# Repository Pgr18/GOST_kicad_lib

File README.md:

# <strong> Схема электрическая принципиальная "Светодиодная цветомузыка" </strong>

Цель работы: реализация схемы электрической принципиальной "Светодиодная цветомузыка" с использованием среды KiCAD.

На рисунке 1 представлена электрическая принципиальная схема светодиодной цветомузыки.  

<image src="https://github.com/Pgr18/GOST_kicad_lib/blob/Prohorova-Christina/Plata%201111.png"  alt="Рисунок 1 - Принципиальная схема устройства">

Рисунок 1 - Принципиальная схема Светодиодной цветомузыки

Для корректной работы устройства необходим усилитель, который является частью схемы, изображенной выше. Принципиальная схема усилителя представлена на рисунке 2.  

<image src="https://github.com/Pgr18/GOST_kicad_lib/blob/Prohorova-Christina/%D0%A0%D0%B8%D1%81%D1%83%D0%BD%D0%BE%D0%BA%202%20%D0%A1%D0%AD%D0%9F%20%D1%83%D1%81%D0%B8%D0%BB%D0%B8%D1%82%D0%B5%D0%BB%D1%8C.jpg"  alt="Рисунок 2 - Принципиальная схема усилителя">

Рисунок 2 - Принципиальная схема усилителя сигнала

Элементная база вышеупомянутой схемы включает в себя:
- Резисторы: 200 Ом – 3 шт., 500 Ом – 2 шт., 1 кОм – 2 шт., 10 кОм – 1 шт,  47 кОм – 1 шт.;
- Подстрочные резисторы: 47 кОм – 3 шт., 100 кОм – 1 шт.;
- Транзисторы: 4 шт.;
- Светодиоды: зеленый - 1 шт., синий - 1 шт., красный - 1 шт.;
- Неполярные конденсаторы: 100 нФ – 1 шт., 150 нФ – 1 шт., 330 нФ – 1 шт., 680 нФ – 1 шт., 10 мкФ – 2 шт

Подбор элементов для реализации схемы осуществлялся с использованием сайта *[ChipDip](https://www.chipdip.ru/)*. После этого для каждого элемента были подобраны посадочные места и модели, взятые из общедоступных источников: *[Snap EDA](https://www.snapeda.com/)* и *[Electronic Component Search Engine](https://componentsearchengine.com/)*.

Следующим этапом был перенос принципиальной схемы на макет печатной платы. В соответствии со связями между элементами была проведена трассировка платы. Ширина дорожек составляла 0,5 мм.

После этого была проведена сплошная заливка макета платы медью. На поверхность платы были нанесены обозначения элементов схемы, а также обозначения внешних контактов платы.

На рисунке 3 представлен результат проделанной работы

<image src="https://github.com/Pgr18/GOST_kicad_lib/blob/Prohorova-Christina/plata11.png" alt="Рисунок 3 - Печатная плата">
Рисунок 3 - Печатная плата

На рисунке 4 представлена 3D-модель печатной платы.

<image src="https://github.com/Pgr18/GOST_kicad_lib/blob/Prohorova-Christina/3dplata.png" alt= "Рисунок 4 - 3D модель печатной платы">
  
Рисунок 4 - 3D модель печатной платы

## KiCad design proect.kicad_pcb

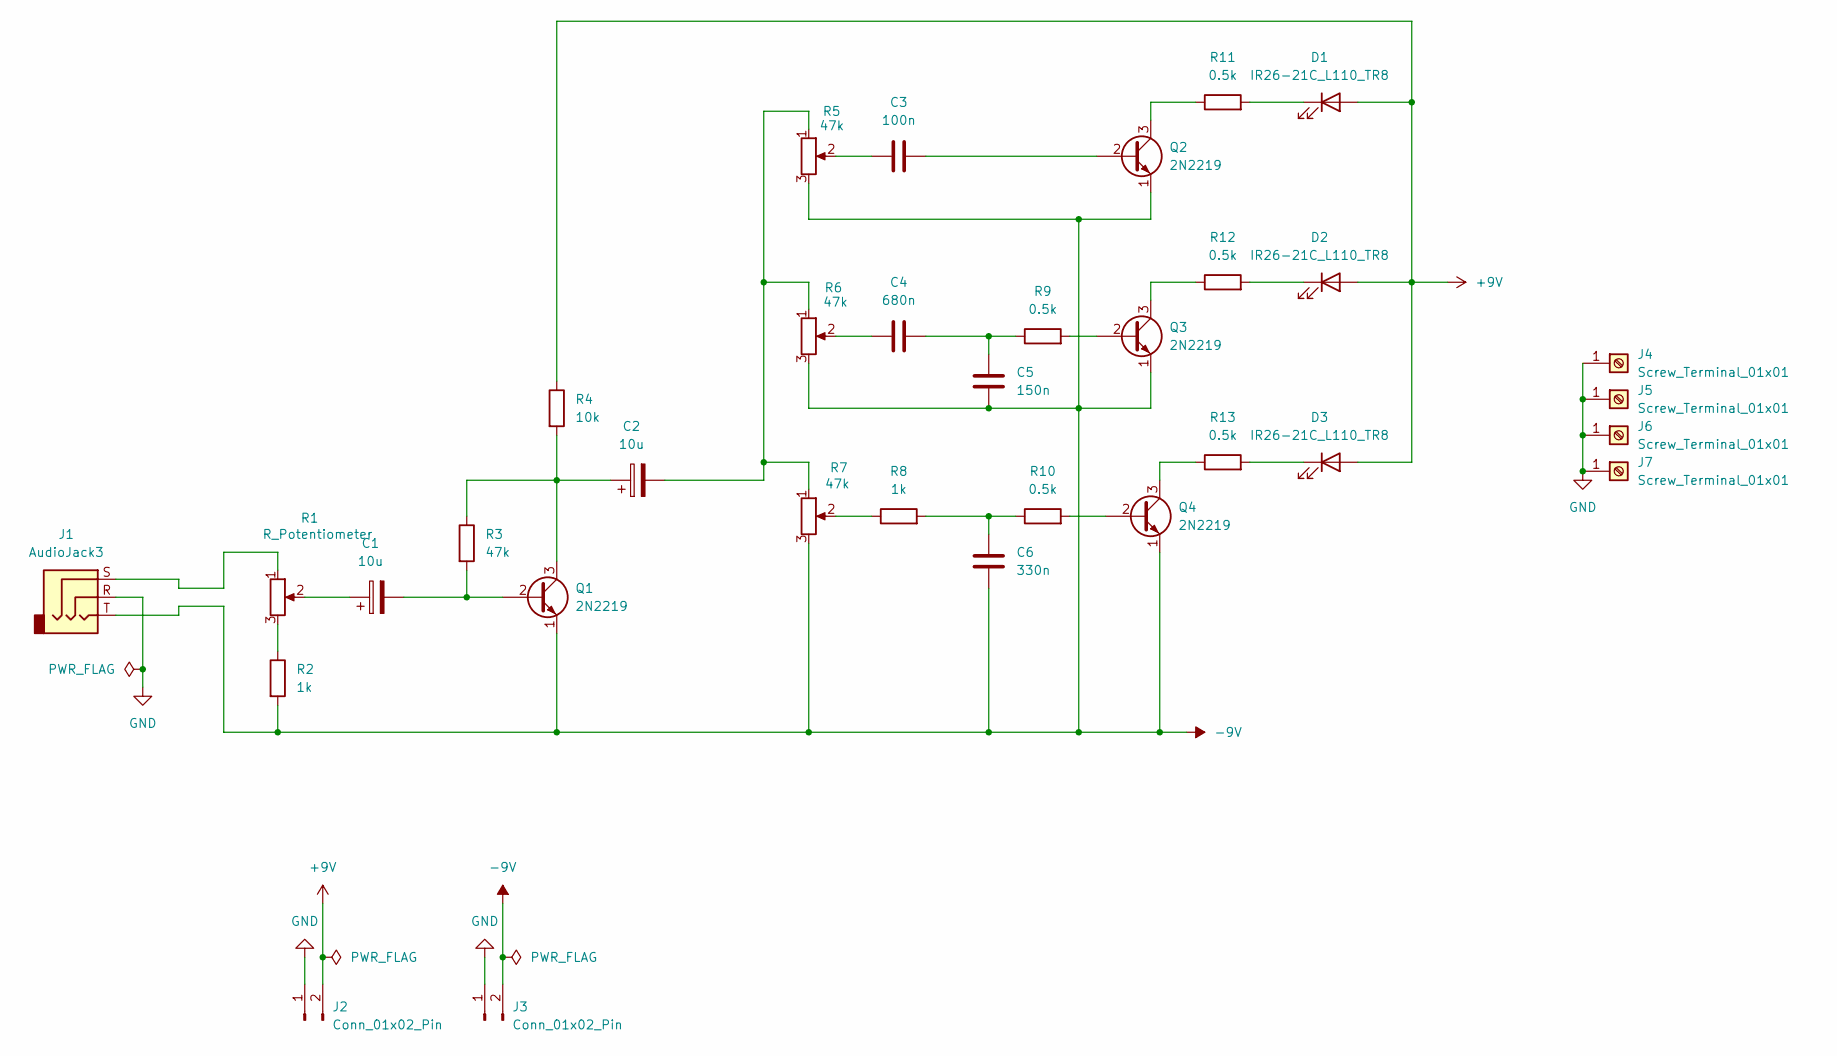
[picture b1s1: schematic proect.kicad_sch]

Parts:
C1, C2: 10u; C_1206_3216Metric
C3: 100n; C_0201_0603Metric
C4: 680n; C_0201_0603Metric
C5: 150n; C_0201_0603Metric
C6: 330n; C_0201_0603Metric
D1, D2, D3: IR26-21C_L110_TR8; LED_1206_3216Metric
J1: AudioJack3; Jack_3.5mm_CUI_SJ-3523-SMT_Horizontal
J2, J3: Conn_01x02_Pin; PinHeader_1x02_P2.54mm_Vertical
J4, J5, J6, J7: Screw_Terminal_01x01; MountingHole_3mm_Pad_Via
Q1, Q2, Q3, Q4: 2N2219; TO-39-3
R1: R_Potentiometer; Potentiometer_ACP_CA6-VSMD_Vertical
R2, R8: 1k; R_0201_0603Metric
R3: 47k; R_0201_0603Metric
R4: 10k; R_0201_0603Metric
R5, R6, R7: 47k; Potentiometer_ACP_CA6-VSMD_Vertical
R9, R10, R11, R12, R13: 0.5k; R_0201_0603Metric

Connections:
+9V: D1.2 (A), D2.2 (A), D3.2 (A), J2.2, R4.1
-9V: C5.1, C6.1, J1.T, J3.2, Q1.1 (E), Q2.1 (E), Q3.1 (E), Q4.1 (E), R2.2, R5.3, R6.3, R7.3
GND: J1.R, J2.1, J3.1, J4.1, J5.1, J6.1, J7.1
unnamed: C1.1, R1.2
unnamed: C2.2, R5.1, R6.1, R7.1
unnamed: C3.1, R5.2
unnamed: C4.1, R6.2
unnamed: C4.2, C5.2, R9.1
unnamed: C6.2, R8.2, R10.1
unnamed: D1.1 (K), R11.2
unnamed: D2.1 (K), R12.2
unnamed: D3.1 (K), R13.2
unnamed: J1.S, R1.1
unnamed: C1.2, Q1.2 (B), R3.2
unnamed: C2.1, Q1.3 (C), R3.1, R4.2
unnamed: C3.2, Q2.2 (B)
unnamed: Q2.3 (C), R11.1
unnamed: Q3.2 (B), R9.2
unnamed: Q3.3 (C), R12.1
unnamed: Q4.2 (B), R10.2
unnamed: Q4.3 (C), R13.1
unnamed: R1.3, R2.1
unnamed: R7.2, R8.1

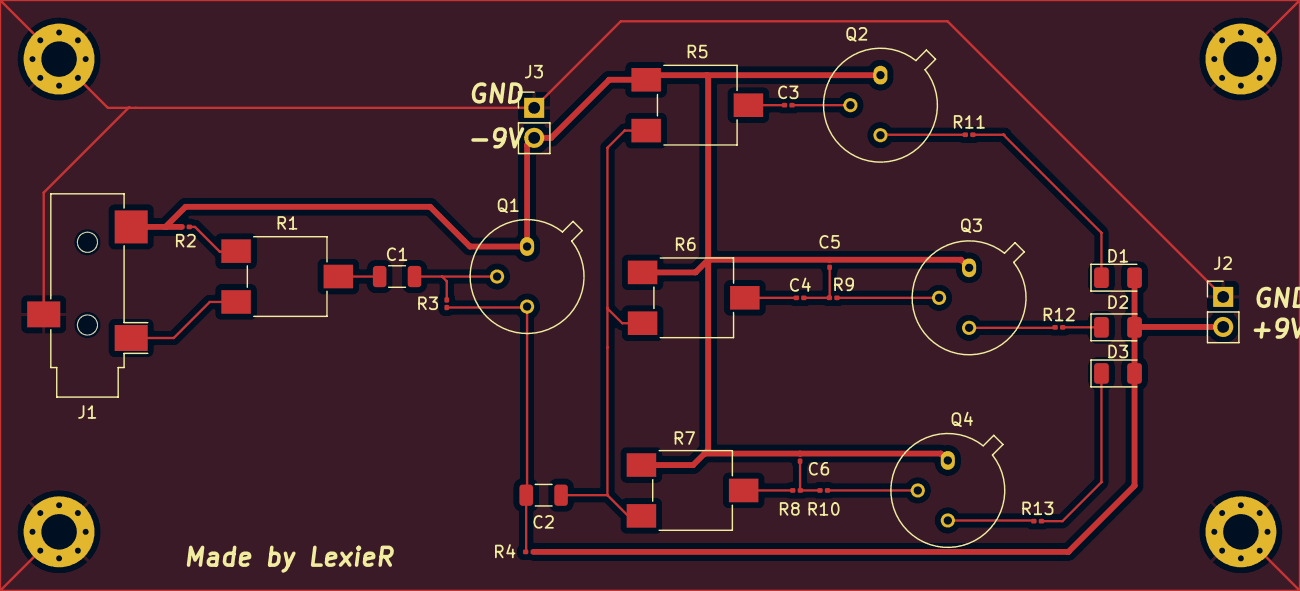
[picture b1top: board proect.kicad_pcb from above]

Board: 2 copper layers, 33 parts (0 on the bottom side), 23 nets.

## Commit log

2024-09-26 Added 0603 resistor
2024-09-26 Added 0603 resistor 2
2024-10-02 Added resistor 1
2024-10-11 Adding components and creating pechatnaya plata
2024-10-29 Done
